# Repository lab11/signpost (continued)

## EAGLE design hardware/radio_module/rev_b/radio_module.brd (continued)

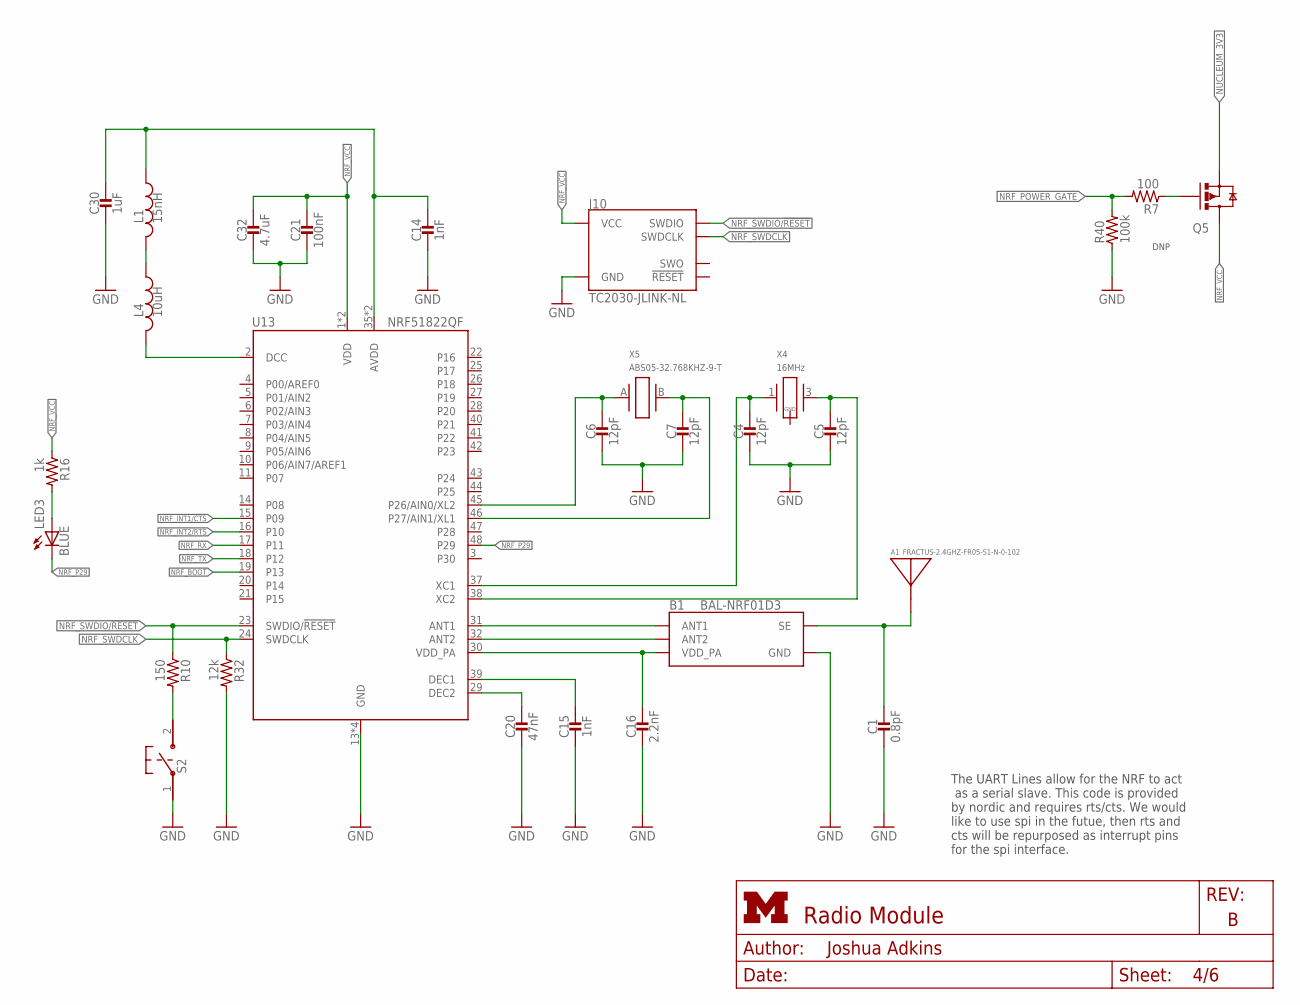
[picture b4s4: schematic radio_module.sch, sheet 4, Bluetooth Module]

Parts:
A1: FRACTUS-2.4GHZ-FR05-S1-N-0-102; FRACTUS-ANTENNA-FR05-S1-N-0-102
B1: BAL-NRF01D3
C1: 0.8pF; 0402_CAP; DIGIKEY 490-6269-1-ND
C4, C5, C6, C7: 12pF; 0402_CAP; DIGIKEY 490-6197-1-ND
C14, C15: 1nF; 0402_CAP; DIGIKEY 490-1303-1-ND
C16: 2.2nF; 0402_CAP; DIGIKEY 490-5419-1-ND
C20: 47nF; 0402_CAP; DIGIKEY 490-3254-1-ND
C21: 100nF; 0402_CAP; DIGIKEY 490-10777-1-ND
C30: 1uF; 0402_CAP; DIGIKEY 490-1320-1-ND
C32: 4.7uF; 0402_CAP; DIGIKEY 490-13252-1-ND
J10: TC2030-JLINK-NL; TC2030-IDC-NL
L1: 15nH; 0402_CAP; DIGIKEY 587-1521-1-ND
L4: 10uH; 0603_CAP; DIGIKEY 490-4025-1-ND
LED3: BLUE; LED-0603; DIGIKEY 511-1578-1-ND
Q5: SI223DDS; SOT23-3
R7: 100; 0402_RES; DIGIKEY 311-100LRCT-ND
R10: 150; 0402_RES; DIGIKEY RHM150CDCT-ND
R16: 1k; 0402_RES; DIGIKEY 311-1.0KJRCT-ND
R32: 12k; 0402_RES; DIGIKEY RHM12.0KCDCT-ND
R40: 100k; 0402_RES; DIGIKEY 311-100KLRCT-ND
S2: B3U-1000P
U13: NRF51822QF; QFN-48-6MM
X4: 16MHz; TXC-8Y; DIGIKEY 887-2003-1-ND
X5: ABS05-32.768KHZ-9-T; ABS05

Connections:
AVDD1: C14.1, C30.1, L1.1, U13.35 (AVDD), U13.36 (AVDD)
DCC1: L4.2, U13.2 (DCC)
GND: B1.GND, C1.2, C4.2, C5.2, C6.2, C7.2, C14.2, C15.2, C16.2, C20.2, C21.2, C30.2, C32.2, J10.5 (GND), R32.2, R40.1, S2.1, U13.13 (GND), U13.33 (GND), U13.34 (GND), U13.GND; also elsewhere on the board
unnamed: Q5.1 (G), R7.1
unnamed: B1.ANT1, U13.31 (ANT1)
unnamed: B1.ANT2, U13.32 (ANT2)
unnamed: A1.1, B1.SE, C1.1
unnamed: L1.2, L4.1
unnamed: C4.1, U13.37 (XC1), X4.1
unnamed: C5.1, U13.38 (XC2), X4.3 (2)
unnamed: C15.1, U13.39 (DEC1)
unnamed: C20.1, U13.29 (DEC2)
unnamed: LED3.A, R16.2
unnamed: R10.2, S2.2
NRF_A2: C7.1, U13.46 (P27/AIN1/XL1), X5.B (2)
NRF_A3: C6.1, U13.45 (P26/AIN0/XL2), X5.A (1)
NRF_BOOT: U13.19 (P13); also elsewhere on the board
NRF_INT1/CTS: U13.15 (P09); also elsewhere on the board
NRF_INT2/RTS: U13.16 (P10); also elsewhere on the board
NRF_P29: LED3.C, U13.48 (P29)
NRF_POWER_GATE: R7.2, R40.2; also elsewhere on the board
NRF_RX: U13.17 (P11); also elsewhere on the board
NRF_SWDCLK: J10.4 (SWDCLK), R32.1, U13.24 (SWDCLK)
NRF_SWDIO/!RESET: J10.2 (SWDIO), R10.1, U13.23 (SWDIO/!RESET); also elsewhere on the board
NRF_TX: U13.18 (P12); also elsewhere on the board
NRF_VCC: C21.1, C32.1, J10.1 (VCC), Q5.3 (D), R16.1, U13.1 (VDD), U13.12 (VDD)
NUCLEUM_3V3: Q5.2 (S); also elsewhere on the board
VDD_PA1: B1.VCC (VDD_PA), C16.1, U13.30 (VDD_PA)

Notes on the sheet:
DNP
The UART Lines allow for the NRF to act as a serial slave. This code is provided by nordic and requires rts/cts. We would like to use spi in the futue, then rts and cts will be repurposed as interrupt pins for the spi interface.

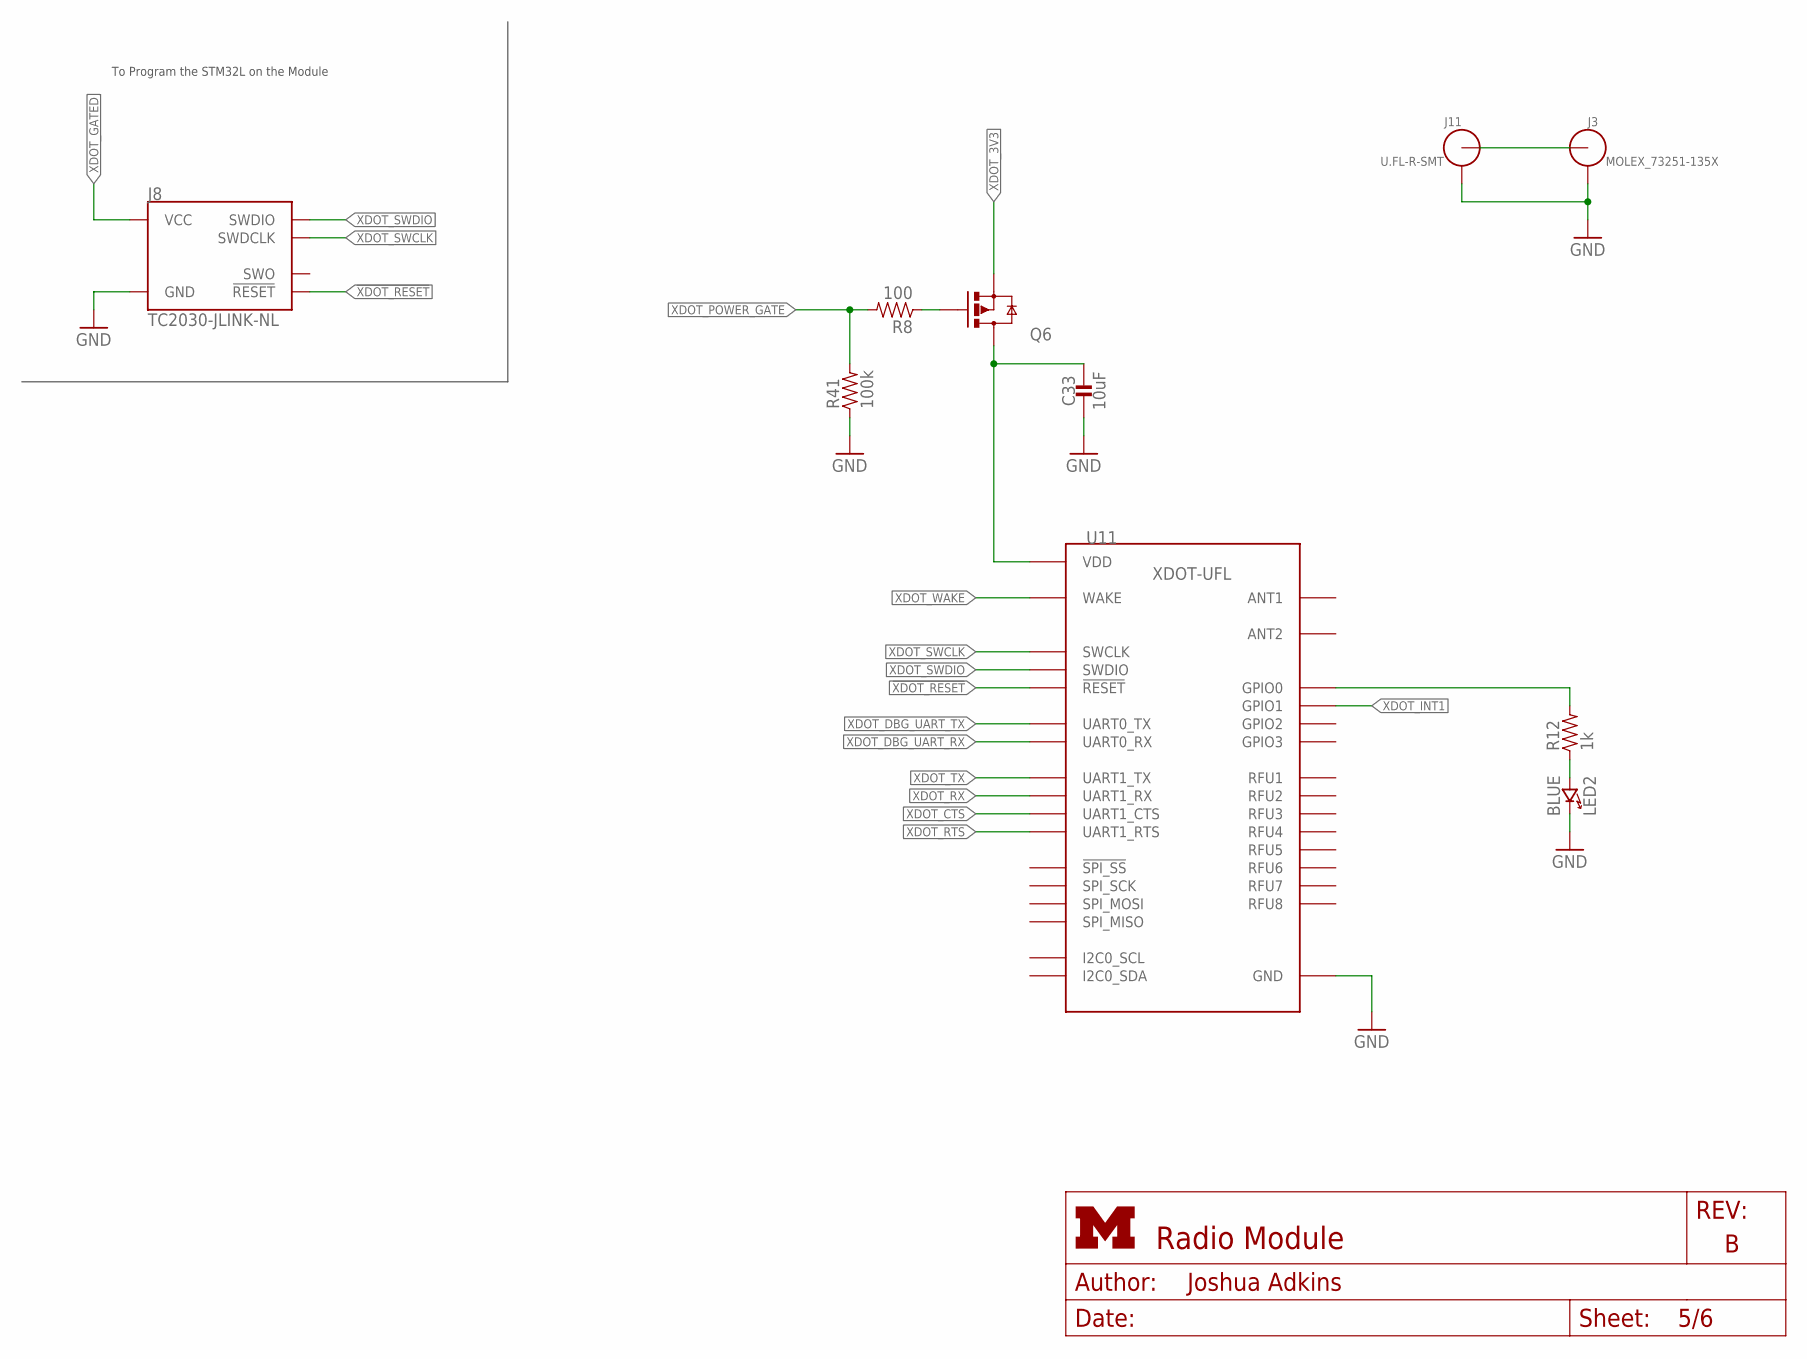
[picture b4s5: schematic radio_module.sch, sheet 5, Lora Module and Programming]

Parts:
C33: 10uF; 0402_CAP; DIGIKEY 490-13233-1-ND
J3: MOLEX_73251-135X; SMA-J/PCB
J8: TC2030-JLINK-NL; TC2030-IDC-NL
J11: U.FL-R-SMT; U.FL_SMT
LED2: BLUE; LED-0603; DIGIKEY 511-1578-1-ND
Q6: SI223DDS; SOT23-3
R8: 100; 0402_RES; DIGIKEY 311-100LRCT-ND
R12: 1k; 0402_RES; DIGIKEY 311-1.0KJRCT-ND
R41: 100k; 0402_RES; DIGIKEY 311-100KLRCT-ND
U11: XDOT_MODULE

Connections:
!XDOT_RESET: J8.3 (!RESET), U11.P$33 (!RESET); also elsewhere on the board
GND: C33.2, J3.2, J3.3, J3.4, J3.5, J8.5 (GND), J11.GND1, J11.GND2, LED2.C (CATHODE), R41.1, U11.P$1 (GND), U11.P$5 (GND), U11.P$17 (GND), U11.P$20 (GND), U11.P$35 (GND), U11.P$36 (GND), U11.P$38 (GND), U11.P$39 (GND), U11.P$40 (GND), U11.P$41 (GND), U11.P$42 (GND), U11.P$43 (GND), U11.P$44 (GND), U11.P$45 (GND), U11.P$46 (GND), U11.P$48 (GND), U11.P$49 (GND), U11.P$50 (GND), U11.P$51 (GND), U11.P$52 (GND), U11.P$53 (GND), U11.P$54 (GND), U11.P$55 (GND), U11.P$56 (GND), U11.P$57 (GND), U11.P$58 (GND); also elsewhere on the board
unnamed: J3.1 (ANT), J11.SIG (ANT)
unnamed: LED2.A (ANODE), R12.1
unnamed: Q6.1 (G), R8.1
XDOT_3V3: Q6.2 (S); also elsewhere on the board
XDOT_CTS: U11.P$32 (UART1_CTS); also elsewhere on the board
XDOT_DBG_UART_RX: U11.P$16 (UART0_RX); also elsewhere on the board
XDOT_DBG_UART_TX: U11.P$15 (UART0_TX); also elsewhere on the board
XDOT_GATED: C33.1, J8.1 (VCC), Q6.3 (D), U11.P$3 (VDD), U11.P$4 (VDD)
XDOT_GPIO0: R12.2, U11.P$26 (GPIO0)
XDOT_INT1: U11.P$25 (GPIO1); also elsewhere on the board
XDOT_POWER_GATE: R8.2, R41.2; also elsewhere on the board
XDOT_RTS: U11.P$31 (UART1_RTS); also elsewhere on the board
XDOT_RX: U11.P$14 (UART1_RX); also elsewhere on the board
XDOT_SWCLK: J8.4 (SWDCLK), U11.P$29 (SWCLK)
XDOT_SWDIO: J8.2 (SWDIO), U11.P$30 (SWDIO)
XDOT_TX: U11.P$13 (UART1_TX); also elsewhere on the board
XDOT_WAKE: U11.P$34 (WAKE); also elsewhere on the board

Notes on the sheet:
To Program the STM32L on the Module

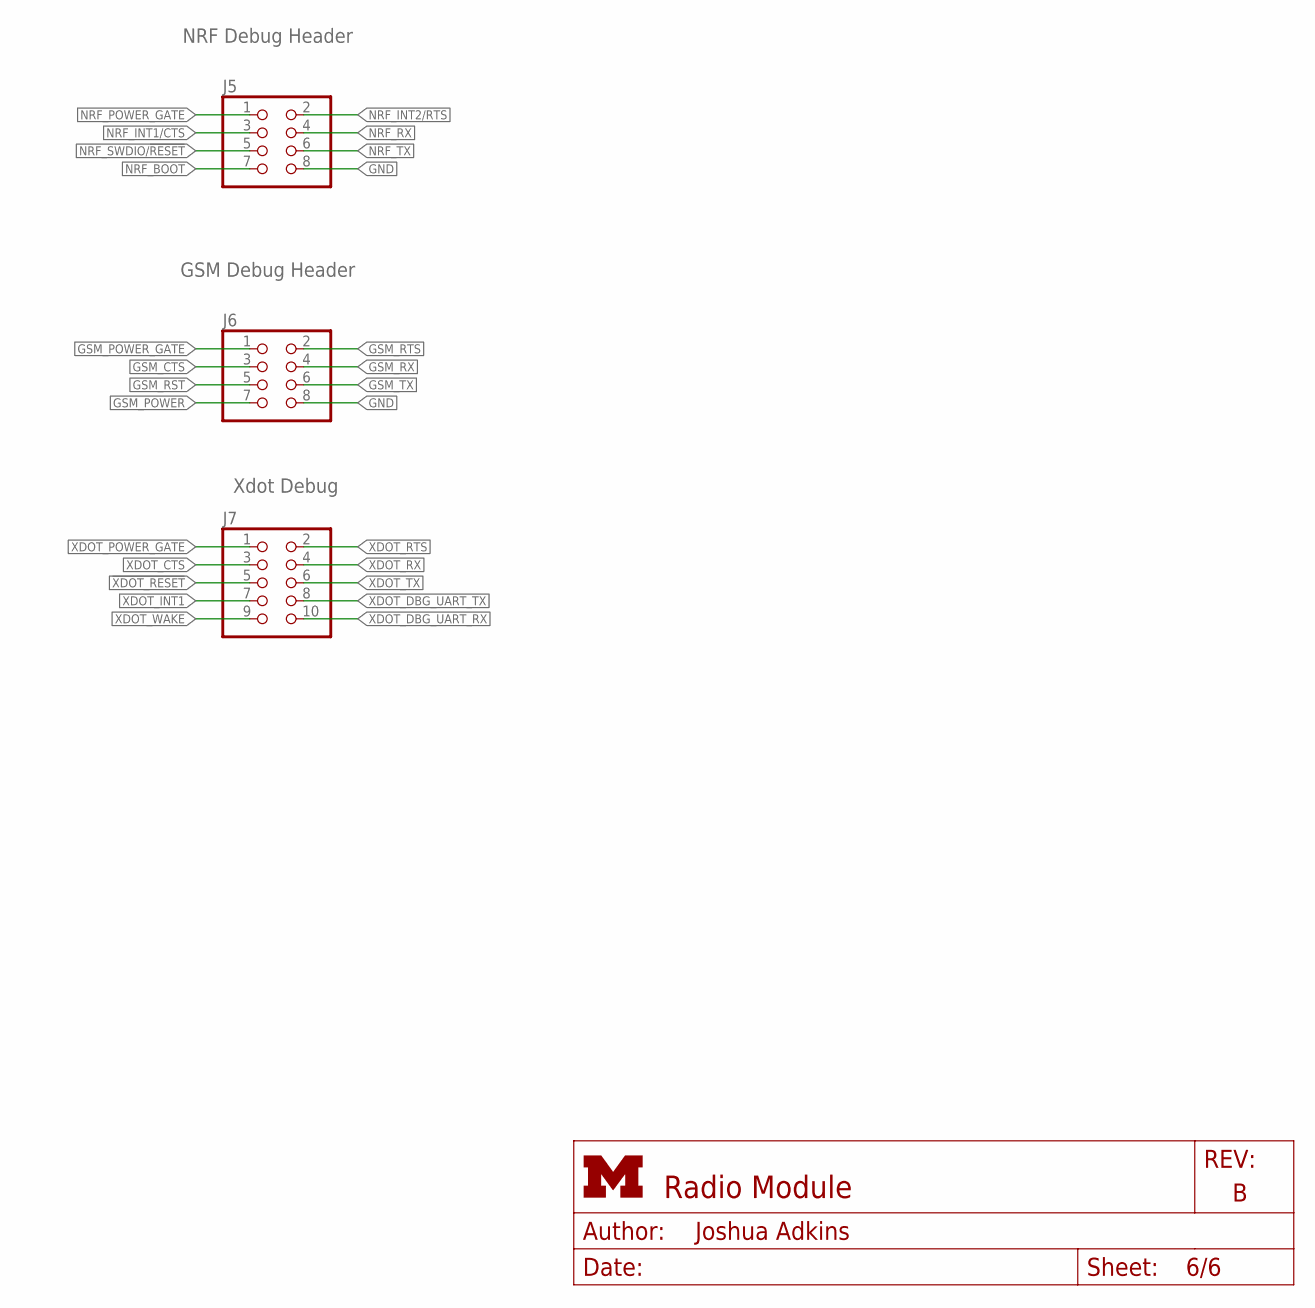
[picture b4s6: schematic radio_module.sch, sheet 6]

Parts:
J5, J6: PINHD-2X4; 2X04; DIGIKEY 952-2123-ND
J7: PINHD-2X5; 2X05; DIGIKEY 609-3243-ND

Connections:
!XDOT_RESET: J7.5; also elsewhere on the board
GND: J5.8, J6.8; also elsewhere on the board
GSM_CTS: J6.3; also elsewhere on the board
GSM_POWER: J6.7; also elsewhere on the board
GSM_POWER_GATE: J6.1; also elsewhere on the board
GSM_RST: J6.5; also elsewhere on the board
GSM_RTS: J6.2; also elsewhere on the board
GSM_RX: J6.4; also elsewhere on the board
GSM_TX: J6.6; also elsewhere on the board
NRF_BOOT: J5.7; also elsewhere on the board
NRF_INT1/CTS: J5.3; also elsewhere on the board
NRF_INT2/RTS: J5.2; also elsewhere on the board
NRF_POWER_GATE: J5.1; also elsewhere on the board
NRF_RX: J5.4; also elsewhere on the board
NRF_SWDIO/!RESET: J5.5; also elsewhere on the board
NRF_TX: J5.6; also elsewhere on the board
XDOT_CTS: J7.3; also elsewhere on the board
XDOT_DBG_UART_RX: J7.10; also elsewhere on the board
XDOT_DBG_UART_TX: J7.8; also elsewhere on the board
XDOT_INT1: J7.7; also elsewhere on the board
XDOT_POWER_GATE: J7.1; also elsewhere on the board
XDOT_RTS: J7.2; also elsewhere on the board
XDOT_RX: J7.4; also elsewhere on the board
XDOT_TX: J7.6; also elsewhere on the board
XDOT_WAKE: J7.9; also elsewhere on the board

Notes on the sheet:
NRF Debug Header
GSM Debug Header
Xdot Debug

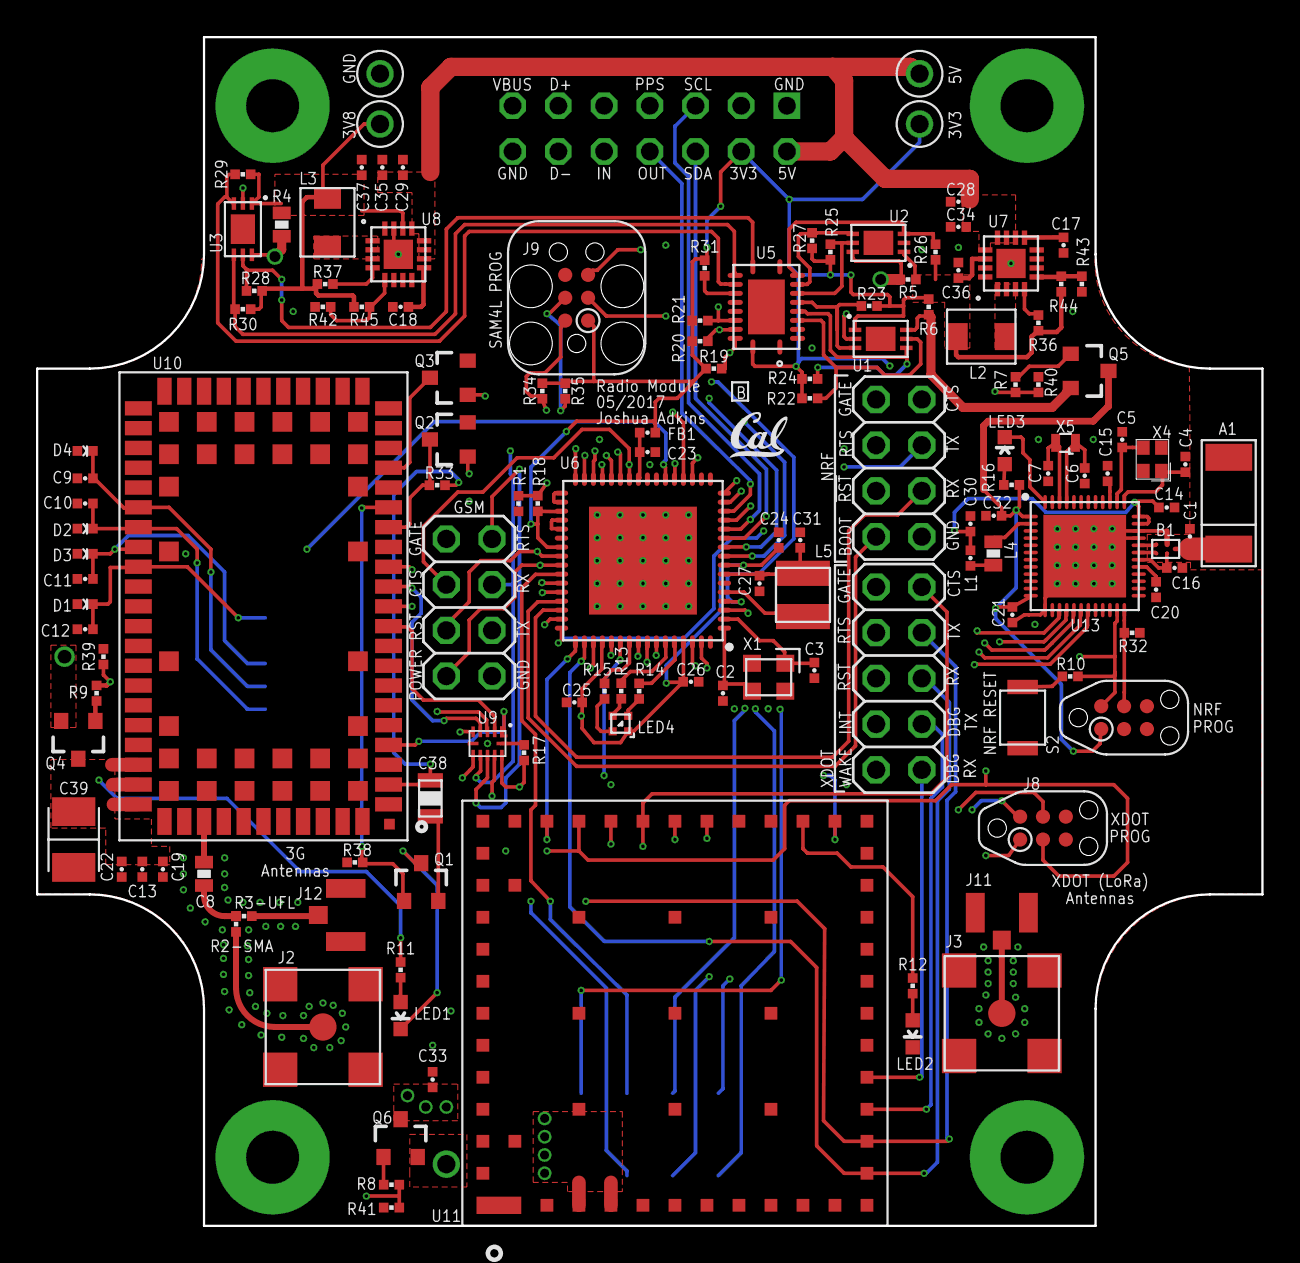
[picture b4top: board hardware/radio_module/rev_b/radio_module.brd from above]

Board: 4 copper layers, 68.1 x 66.0 mm, 138 parts (1 on the bottom side), 128 nets.

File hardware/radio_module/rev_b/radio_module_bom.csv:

# Bill of Materials,,,,,,,,,,,,,,,,,
# Converted from {},,,,,,,,,,,,,,,,,
# Generated by bom_to_text.py,,,,,,,,,,,,,,,,,
#,,,,,,,,,,,,,,,,,
,,,,,,,,,,,,,,,,,
Qty,Value,Device,Package,Parts,Description,DIGIKEY,DIGIKEY1,DIGIKEY2,DNP,MF,MF1,MF2,MFN,MFN1,MFN2,MOUSER,RICHARDSON_RFPD
2,,PINHD-2X4,2X04,"J5, J6",PIN HEADER,952-2123-ND,,,,,,,,,,,
1,,PINHD-2X5,2X05,J7,PIN HEADER,609-3243-ND,,,,,,,,,,,
3,0,RESISTOR0402_RES,0402_RES,"R1, R2, R3",Resistor,311-0.0JRCT-ND,,,,,,,,,,,
1,0.015,RESISTOR0603_RES,0603-RES,R4,Resistor,408-1406-1-ND ,,,,,,,,,,,
1,0.43,RESISTOR0402_RES,0402_RES,R5,Resistor,P.43AKCT-ND ,,,,,,,,,,,
1,0.8pF,CAPACITOR0402_CAP,0402_CAP,C1,SMD Capacitor,490-6269-1-ND,,,,,,,,,,,
1,1.5k,FERRITE_BEAD0402,0402_CAP,FB1,,445-2158-1-ND,,,,,,,,,,,
3,100,RESISTOR0402_RES,0402_RES,"R7, R8, R9",Resistor,311-100LRCT-ND,,,,,,,,,,,
9,100k,RESISTOR0402_RES,0402_RES,"R33, R34, R35, R36, R37, R38, R39, R40, R41",Resistor,311-100KLRCT-ND ,,,,,,,,,,,
9,100nF,CAPACITOR0402_CAP,0402_CAP,"C21, C22, C23, C24, C25, C26, C27, C28, C29",SMD Capacitor,490-10777-1-ND,,,,,,,,,,,
1,100uF,CAPACITOR0805_CAP,0805_CAP,C38,SMD Capacitor,490-13981-1-ND,,,,,,,,,,,
14,10k,RESISTOR0402_RES,0402_RES,"R17, R19, R20, R21, R22, R23, R24, R25, R26, R27, R28, R29, R30, R31",Resistor,311-10KJRCT-ND ,,,,,,,,,,,
1,10k,RESISTOR0402_RES,0402_RES,R18,Resistor,311-10KJRCT-ND ,,,DNP,,,,,,,,
1,10nF,CAPACITOR0402_CAP,0402_CAP,C19,SMD Capacitor,490-4516-1-ND ,,,,,,,,,,,
3,10uF,CAPACITOR0402_CAP,0402_CAP,"C33, C34, C35",SMD Capacitor,490-13233-1-ND,,,,,,,,,,,
1,10uH,INDUCTOR0603,0603_CAP,L4,A very specific inductor,490-4025-1-ND,,,,,,,,,,,
1,12k,RESISTOR0402_RES,0402_RES,R32,Resistor,RHM12.0KCDCT-ND,,,,,,,,,,,
4,12pF,CAPACITOR0402_CAP,0402_CAP,"C4, C5, C6, C7",SMD Capacitor,490-6197-1-ND,,,,,,,,,,,
4,14V,DIODE_ZENER0402,0402_DIODE,"D1, D2, D3, D4",,PESD0402-140CT-ND ,,,,,,,,,,,
1,150,RESISTOR0402_RES,0402_RES,R10,Resistor,RHM150CDCT-ND,,,,,,,,,,,
1,15nH,INDUCTOR0402,0402_CAP,L1,A very specific inductor,587-1521-1-ND,,,,,,,,,,,
1,16 MHz,FH1600015,FHXXX,X1,Pericom Type FH 16 MHz 2.5 x 2.0 mm,FH1600015CT-ND,,,,,,,,,,,
1,16MHz,TXC-8Y,TXC-8Y,X4,2mmx1.6mm SMD Crystal,887-2003-1-ND,,,,,,,,,,,
6,1k,RESISTOR0402_RES,0402_RES,"R11, R12, R13, R14, R15, R16",Resistor,311-1.0KJRCT-ND,,,,,,,,,,,
2,1nF,CAPACITOR0402_CAP,0402_CAP,"C14, C15",SMD Capacitor,490-1303-1-ND,,,,,,,,,,,
1,1uF,CAPACITOR0402_CAP,0402_CAP,C30,SMD Capacitor,490-1320-1-ND,,,,,,,,,,,
1,2.2nF,CAPACITOR0402_CAP,0402_CAP,C16,SMD Capacitor,490-5419-1-ND,,,,,,,,,,,
2,2.2uH,INDUCTORIHL,IHL-1212BZ-11,"L2, L3",A very specific inductor,541-1322-1-ND,,,,Vishay Dale,,,IHLP1212BZER2R2M11,,,,
1,200k,RESISTOR0402_RES,0402_RES,R42,Resistor,P200KLCT-ND ,,,,,,,,,,,
1,220uF,CAPACITOR1210_CAP,1210_CAP,C39,SMD Capacitor,1276-3375-1-ND ,,,,,,,,,,,
2,22uF,CAPACITOR0402_CAP,0402_CAP,"C36, C37",SMD Capacitor,1276-6834-1-ND ,,,,,,,,,,,
1,22uH,LHQ3NP,1212,L5,LHQ3NP Inductor,490-5350-1-ND,,,,,,,,,,,
1,240k,RESISTOR0402_RES,0402_RES,R43,Resistor,YAG3291CT-ND ,,,,,,,,,,,
1,3.32,RESISTOR0402_RES,0402_RES,R6,Resistor,541-3.32LLCT-ND ,,,,,,,,,,,
2,3.3nF,CAPACITOR0402_CAP,0402_CAP,"C17, C18",SMD Capacitor,490-3248-1-ND,,,,,,,,,,,
1,33pF,CAPACITOR0603_CAP,0603_CAP,C8,SMD Capacitor,712-1342-1-ND,,,,,,,,,,,
2,4.7uF,CAPACITOR0402_CAP,0402_CAP,"C31, C32",SMD Capacitor,490-13252-1-ND,,,,,,,,,,,
1,47nF,CAPACITOR0402_CAP,0402_CAP,C20,SMD Capacitor,490-3254-1-ND,,,,,,,,,,,
3,47pF,CAPACITOR0402_CAP,0402_CAP,"C10, C11, C12",SMD Capacitor,490-6241-1-ND ,,,,,,,,,,,
1,47pF,CAPACITOR0402_CAP,0402_CAP,C9,SMD Capacitor,490-6241-1-ND,,,,,,,,,,,
1,56pF,CAPACITOR0402_CAP,0402_CAP,C13,SMD Capacitor,490-1288-1-ND ,,,,,,,,,,,
2,750k,RESISTOR0402_RES,0402_RES,"R44, R45",Resistor,YAG3228CT-ND ,,,,,,,,,,,
2,8pF,CAPACITOR0402_CAP,0402_CAP,"C2, C3",SMD Capacitor,490-8230-1-ND,,,,,,,,,,,
1,ABS05-32.768KHZ-9-T,ABS05-32.768KHZ-9-T,ABS05,X5,32.768kHz Crystal,535-11897-1-ND,,,,Abracon,,,ABS05-32.768KHZ-9-T,,,,
1,B3U-1000P,B3U-1000P,B3U-1000P,S2,Switch,SW1020CT-ND,,,,Omron,,,B3U-1000P,,,,
1,BAL-NRF01D3,BAL-NRF01D3,BAL-NRF01D3,B1,"50 ohm nominal input / conjugate match balun to nRF51422-QFAA,",497-13637-1-ND,,,,,,,,,,511-BAL-NRF01D3,
3,BLUE,LED0603,LED-0603,"LED1, LED2, LED3",LEDs,511-1578-1-ND ,,,,,,,,,,,
1,FRACTUS-2.4GHZ-FR05-S1-N-0-102,FRACTUS-2.4GHZ-FR05-S1-N-0-102,FRACTUS-ANTENNA-FR05-S1-N-0-102,A1,"Fractus Compact Reach XtendTM chip antenna is engineered specifically for Bluetooth,",,,,,,,,,,,,FR05-S1-N-0102B
3,LTC2941,LTC2941,DFN-6-2MMX3MM,"U1, U2, U3",I2C Battery Gas Gauge,LTC2941IDCB#TRMPBFCT-ND,,,,,,,,,,,
1,MODULE_GENERIC_DEBUGSMT,MODULE_GENERIC_DEBUGSMT,MODULE_GENERIC_DEBUG_SMT,J1,The debug version of the signpost module header,,S9170-ND,WM17450-ND,,,Sullins,Molex,,SBH11-PBPC-D07-ST-BK,15912080,,
2,MOLEX_73251-135X,MOLEX_73251-135X,SMA-J/PCB,"J2, J3",SMA JACK SMT 50 OHM,WM9357-ND,,,,Molex,,,732511350,,,,
3,MOSFET-NCHANNELSMD,MOSFET-NCHANNELSMD,SOT23-3,"Q1, Q2, Q3",Generic NMOS footprint,2N7002LT1GOSCT-ND,,,,,,,,,,,
1,NANO_SIM,NANO_SIM,WURTH_NANO_SIM,J4,WURTH Nano SIM Connector,732-5954-1-ND,,,,,,,,,,,
1,NRF51822QF,NRF51822QF,QFN-48-6MM,U13,Multiprotocol Bluetooth® 4.0 low energy/2.4 GHz RF SoC,1490-1049-1-ND,,,,,,,,,,949-NRF51822-QFAC-R7,
1,PCA9544AQFN-N20,PCA9544AQFN-N20,QFN-N20,U5,1-4 I2C/SMBUS Multiplexer with interrupt for power supply coulomb counters,296-20960-1-ND,,,,,,,,,,,
1,SAM4LC8BA,SAM4LC8BA,QFN-64-9MM,U6,SAM4L Microcontroller. 64QFN Package. 512 Flash.,ATSAM4LC8BA-MU,,,,,,,,,,,
3,SI223DDS,SI223DDS,SOT23-3,"Q4, Q5, Q6",6A SOT-23 P Fet,SI2333DDS-T1-GE3CT-ND,,,,,,,,,,,
1,SML-LX0404SIUPGUSB,SML-LX0404SIUPGUSB,1MM_SQ_4PAD,LED4,1mm^2 RGB LED,67-2125-1-ND,,,,,,,,,,,
4,TEST_POINT_0.040IN,TEST_POINT_0.040IN,TESTPOINT_0.040IN,"TP1, TP2, TP3, TP4",0.040in Test Point,5001K-ND,,,,,,,,,,,
2,TLV62130,TLV62130,TQFN-16/3MM,"U7, U8","High Efficient 3A switching step-down regulator. 1V-5V out, 4V-17V in.",296-35978-1-ND,,,,Texas Instruments,,,TLV62130RGTR,,,,
1,TXB0104RUT,TXB0104RUT,UQFN-12,U9,4-channel bidirectional level translater,296-25888-1-ND,,,,,,,,,,,
2,U.FL-R-SMT,U.FL-R-SMT,U.FL_SMT,"J11, J12",U.FL-R-SMT Antenna Connector,H122041-ND,,,,Hirose,,,U.FL-R-SMT-1(01),,,,
1,UBLOX_SARA_G350,UBLOX_SARA_G350,UBLOX_SARA_G3,U10,Sara G350 2.5G Radio Module,,,,,,,,,,,,
1,XDOT_MODULE,XDOT_MODULE,XDOT_MODULE,U11,Multitech XDOT LoRa Module,,,,,,,,,,,,
